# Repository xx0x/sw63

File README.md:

# Space Watch SW63

Sci-fi inspired electronic watch.

*MK4 in the development, out in 2026.*

## How to tell the time?

When the button is briefly pressed, SW63 tells you the time using a sequence of LED blinks. It's not a binary clock, it's inspired by the analog clock hands movement and uses quarters, halves and so on; similar to how people used to tell the time before the digital clock became popular.
  
**16:35**  
*half past - four - hours - and - five - minutes - PM*

**6:57**  
*three - minutes - to - whole - seven - hours*

Language can be changed in the watch menu to reflect the different ways different languages express the time ("half past five" in English is "half of six" in German etc).

See [LANGUAGES.md](./LANGUAGES.md) for the full list and examples.

## Controls

**Short press:** Show the time  
**Long press:** Enter Menu (setting the language and time)  
**Extra long press:** Enter Secret settings  
**Multiple short presses:** Show animation

*In Menu / Secret settings:*  
**Short press:** Change  
**Long press:** Confirm and go to next

## BOM (DIY Kits)

| Name                                | Part Number                                   | Qty |
| ----------------------------------- | --------------------------------------------- | --- |
| PCB with assembled SMD components   | custom part                                   | 1   |
| Red 5 mm LED                        | LL-503VD2E-V1-4D                              | 1   |
| Green 5 mm LED                      | LL-504PGD2E-G5-2B                             | 1   |
| Blue 5 mm LED                       | LL-504BD2E-B4-2B                              | 1   |
| Yellow 5 mm LED                     | N0Y64L35<br> L-53SYD<br> L-53SYDK             | 1   |
| Yellow 3×2 mm LED                   | LL-234YD2Q-1B                                 | 4   |
| Red 3 mm LED                        | FYL-3014LRD1A<br> FYL-3014SRT1A               | 1   |
| Li-Po battery LP301020 or LP301120* | AKY0471<br> SparkFun 13852<br> SparkFun 25270 | 1   |
| CNC aluminium enclosure             | custom part                                   | 1   |
| Screw M1.6 length 4mm (hex socket)  | -                                             | 4   |
| 18 mm watch spring bar              | -                                             | 2   |
| 18 mm watch strap                   | -                                             | 1   |

> [!WARNING]
> \***Note:** Due to the shipping restrictions the Li-Po battery isn't part of the DIY Kit. Please provide your own 40 mAh battery with dimensions 20 mm × 11 mm × 3 mm (or smaller) with the integrated protection circuit.

## License

**Schematics, Hardware Designs**  
CERN-OHL-P-2.0

**Code**  
MIT

**Visual elements, Graphics, Documentation**  
CC BY-SA 4.0

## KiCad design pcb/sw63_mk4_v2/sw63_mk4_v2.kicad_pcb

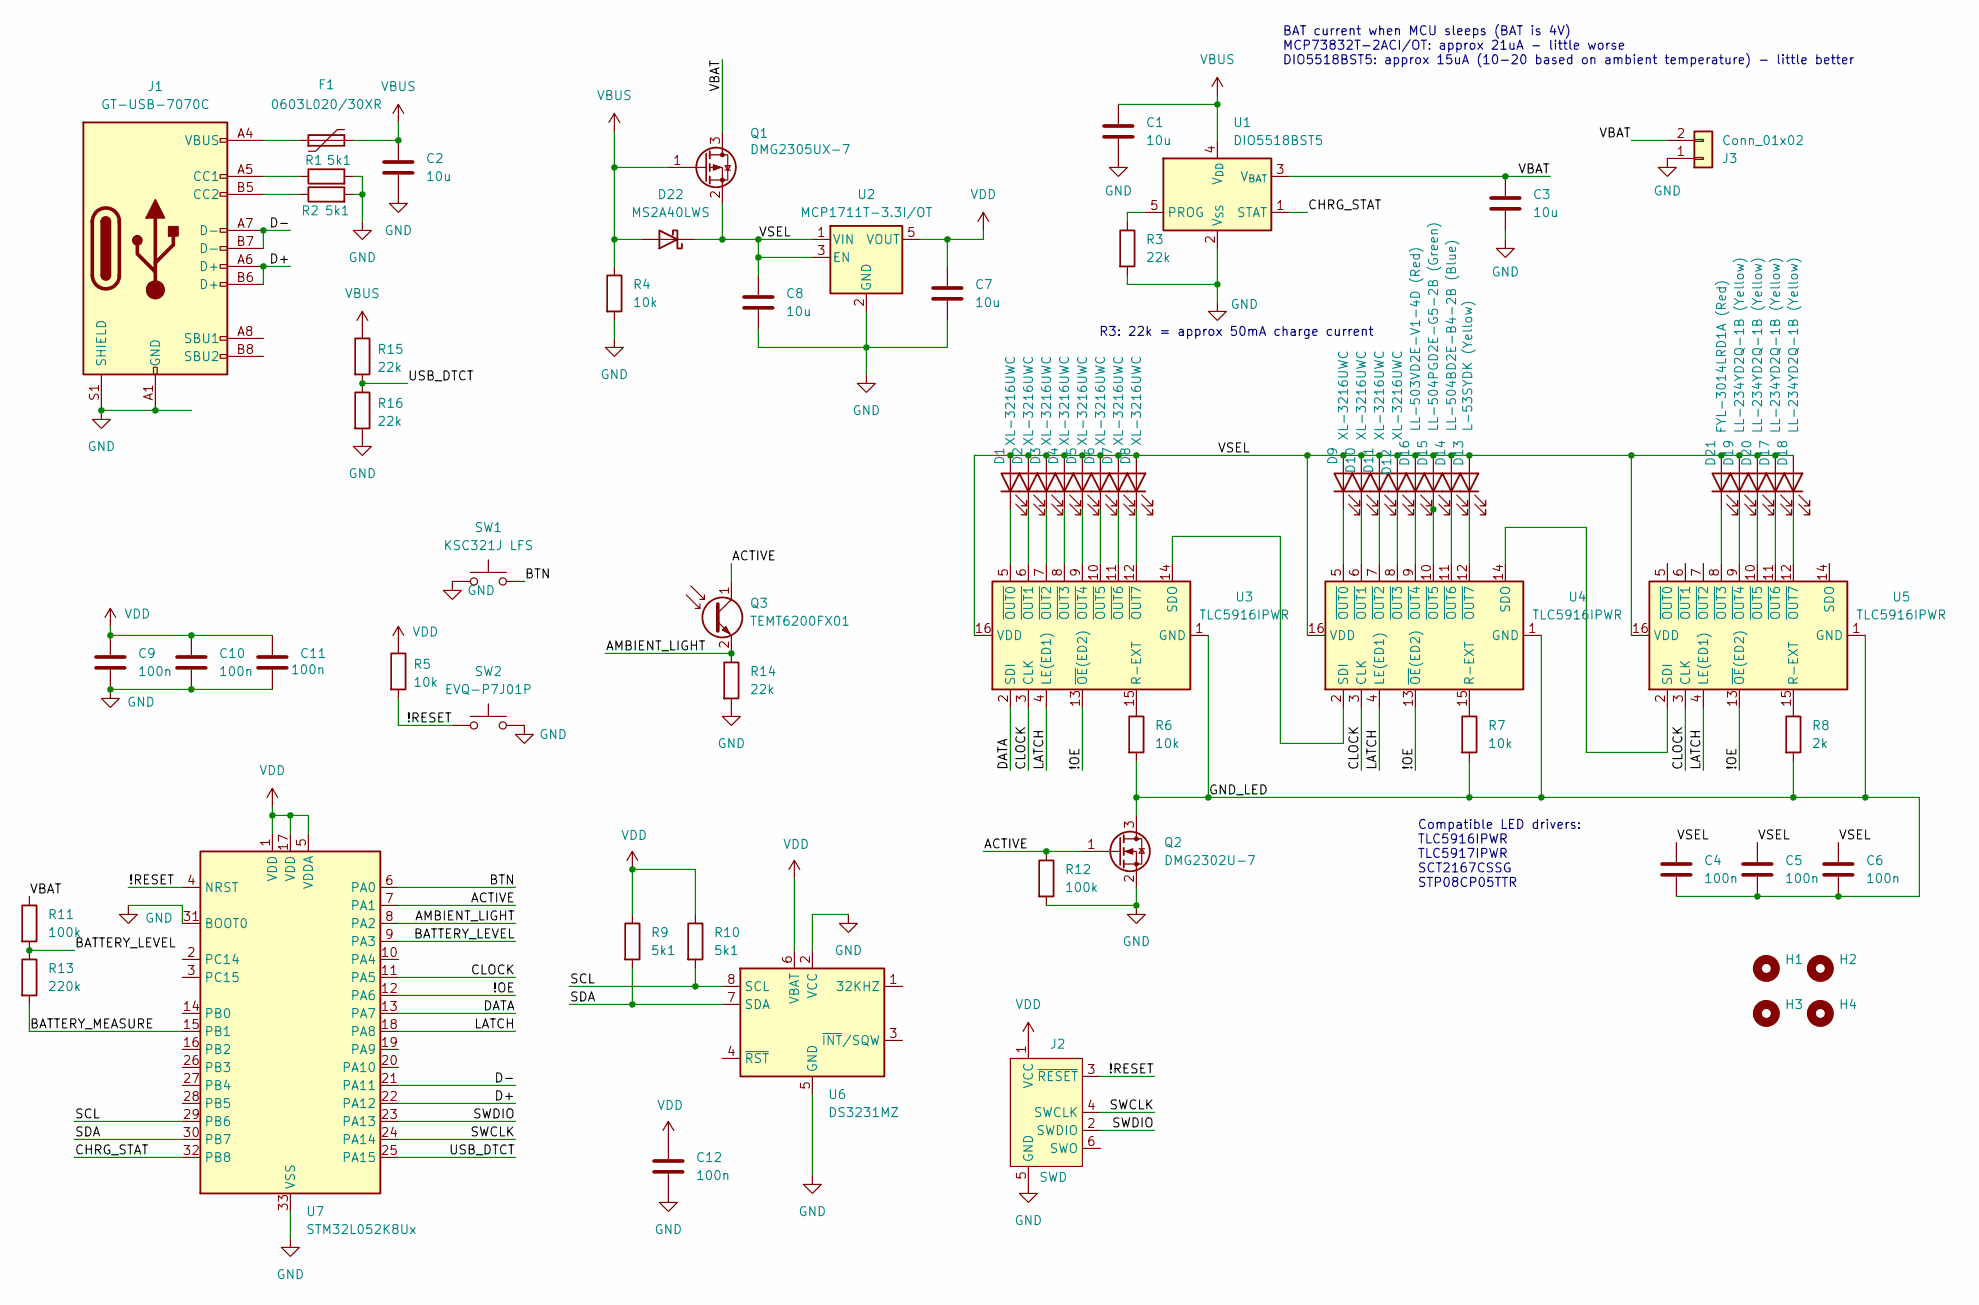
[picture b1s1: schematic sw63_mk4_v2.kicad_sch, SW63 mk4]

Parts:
C1, C2, C3, C7, C8: 10u; C_0402_1005Metric; LCSC C315248
C4, C5, C6, C9, C10, C11, C12: 100n; C_0402_1005Metric; LCSC C1525
D1, D2, D3, D4, D5, D6, D7, D8, D9, D10, D11, D12: XL-3216UWC; LED_1206_W; LCSC C965828
D13: L-53SYDK (Yellow); LED_D5.0mm_Y
D14: LL-504BD2E-B4-2B (Blue); LED_D5.0mm_B
D15: LL-504PGD2E-G5-2B (Green); LED_D5.0mm_G
D16: LL-503VD2E-V1-4D (Red); LED_D5.0mm_R
D17, D18, D19, D20: LL-234YD2Q-1B (Yellow); LED_W3.0mm_H2.0mm_Y
D21: FYL-3014LRD1A (Red); LED_D3.0mm_R
D22: MS2A40LWS; D_SOD-323; LCSC C7380001
F1: 0603L020/30XR; Fuse_0603_1608Metric; LCSC C20608677
H1, H2, H3, H4: MountingHole; MountingHole_1.6mm
J1: GT-USB-7070C; LCSC C5446864
J2: SWD; SWD_2x03_SMD
J3: Conn_01x02; BAT
Q1: DMG2305UX-7; SOT-23; LCSC C150470
Q2: DMG2302U-7; SOT-23
Q3: TEMT6200FX01; LCSC C143695
R1, R2, R9, R10: 5k1; R_0402_1005Metric; LCSC C25905
R3, R14, R15, R16: 22k; R_0402_1005Metric; LCSC C25768
R4, R5, R6, R7: 10k; R_0402_1005Metric; LCSC C25744
R8: 2k; R_0402_1005Metric; LCSC C4109
R11, R12: 100k; R_0402_1005Metric; LCSC C25741
R13: 220k; R_0402_1005Metric; LCSC C25767
SW1: KSC321J LFS; SW_Push_1P1T_NO_CK_KSC3xxJ; LCSC C2798494
SW2: ﻿EVQ-P7J01P; SW_SPST_EVQP7A; LCSC C2828254
U1: DIO5518BST5; SOT-23-5; LCSC C38066
U2: MCP1711T-3.3I/OT; SOT-23-5; LCSC C79527
U3, U4, U5: TLC5916IPWR; TSSOP-16_4.4x5mm_P0.65mm; LCSC C193571
U6: DS3231MZ; SOIC-8_3.9x4.9mm_P1.27mm; LCSC C107410
U7: STM32L052K8Ux; QFN-32-1EP_5x5mm_P0.5mm_EP3.45x3.45mm; LCSC C1342049

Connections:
/!OE: U3.13 (~OE(ED2)), U4.13 (~OE(ED2)), U5.13 (~OE(ED2)), U7.12 (PA6)
/!RESET: J2.3 (~RESET), R5.2, SW2.1, U7.4 (NRST)
/ACTIVE: Q2.1 (G), Q3.1 (C), R12.1, U7.7 (PA1)
/AMBIENT_LIGHT: Q3.2 (E), R14.1, U7.8 (PA2)
/BATTERY_LEVEL: R11.2, R13.1, U7.9 (PA3)
/BATTERY_MEASURE: R13.2, U7.15 (PB1)
/BTN: SW1.2, U7.6 (PA0)
/CHRG_STAT: U1.1 (STAT), U7.32 (PB8)
/CLOCK: U3.3 (CLK), U4.3 (CLK), U5.3 (CLK), U7.11 (PA5)
/D+: J1.A6 (D+), J1.B6 (D+), U7.22 (PA12)
/D-: J1.A7 (D-), J1.B7 (D-), U7.21 (PA11)
/DATA: U3.2 (SDI), U7.13 (PA7)
/GND_LED: C4.2, C5.2, C6.2, Q2.3 (D), R6.2, R7.2, R8.2, U3.1 (GND), U4.1 (GND), U5.1 (GND)
/LATCH: U3.4 (LE(ED1)), U4.4 (LE(ED1)), U5.4 (LE(ED1)), U7.18 (PA8)
/SCL: R10.2, U6.8 (SCL), U7.29 (PB6)
/SDA: R9.2, U6.7 (SDA), U7.30 (PB7)
/SWCLK: J2.4 (SWCLK), U7.24 (PA14)
/SWDIO: J2.2 (SWDIO), U7.23 (PA13)
/USB_DTCT: R15.2, R16.1, U7.25 (PA15)
/VBAT: C3.1, J3.2, Q1.3 (D), R11.1, U1.3 (V_{BAT})
/VSEL: C4.1, C5.1, C6.1, C8.1, D1.2 (A), D2.2 (A), D3.2 (A), D4.2 (A), D5.2 (A), D6.2 (A), D7.2 (A), D8.2 (A), D9.2 (A), D10.2 (A), D11.2 (A), D12.2 (A), D13.2 (A), D14.2 (A), D15.2 (A), D16.2 (A), D17.2 (A), D18.2 (A), D19.2 (A), D20.2 (A), D21.2 (A), D22.1 (K), Q1.2 (S), U2.1 (VIN), U2.3 (EN), U3.16 (VDD), U4.16 (VDD), U5.16 (VDD)
GND: C1.2, C2.2, C3.2, C7.2, C8.2, C9.2, C10.2, C11.2, C12.2, J1.A1 (GND), J1.A12 (GND), J1.B1 (GND), J1.B12 (GND), J1.S1 (SHIELD), J2.5 (GND), J3.1, Q2.2 (S), R1.2, R2.2, R3.2, R4.2, R12.2, R14.2, R16.2, SW1.1, SW2.2, U1.2 (V_{SS}), U2.2 (GND), U6.2 (VCC), U6.5 (GND), U7.31 (BOOT0), U7.33 (VSS)
unnamed: D1.1 (K), U3.5 (~OUT0)
unnamed: D2.1 (K), U3.6 (~OUT1)
unnamed: D3.1 (K), U3.7 (~OUT2)
unnamed: D4.1 (K), U3.8 (~OUT3)
unnamed: D5.1 (K), U3.9 (~OUT4)
unnamed: D6.1 (K), U3.10 (~OUT5)
unnamed: D7.1 (K), U3.11 (~OUT6)
unnamed: D8.1 (K), U3.12 (~OUT7)
unnamed: D9.1 (K), U4.5 (~OUT0)
unnamed: D10.1 (K), U4.6 (~OUT1)
unnamed: D11.1 (K), U4.7 (~OUT2)
unnamed: D12.1 (K), U4.8 (~OUT3)
unnamed: D13.1 (K), U4.12 (~OUT7)
unnamed: D14.1 (K), U4.11 (~OUT6)
unnamed: D15.1 (K), U4.10 (~OUT5)
unnamed: D16.1 (K), U4.9 (~OUT4)
unnamed: D17.1 (K), U5.11 (~OUT6)
unnamed: D18.1 (K), U5.12 (~OUT7)
unnamed: D19.1 (K), U5.9 (~OUT4)
unnamed: D20.1 (K), U5.10 (~OUT5)
unnamed: D21.1 (K), U5.8 (~OUT3)
unnamed: F1.1, J1.A4 (VBUS), J1.A9 (VBUS), J1.B4 (VBUS), J1.B9 (VBUS)
unnamed: J1.A5 (CC1), R1.1
unnamed: J1.B5 (CC2), R2.1
unnamed: R3.1, U1.5 (PROG)
unnamed: R6.1, U3.15 (R-EXT)
unnamed: U3.14 (SDO), U4.2 (SDI)
unnamed: R7.1, U4.15 (R-EXT)
unnamed: U4.14 (SDO), U5.2 (SDI)
unnamed: R8.1, U5.15 (R-EXT)
VBUS: C1.1, C2.1, D22.2 (A), F1.2, Q1.1 (G), R4.1, R15.1, U1.4 (V_{DD})
VDD: C7.1, C9.1, C10.1, C11.1, C12.1, J2.1 (VCC), R5.1, R9.1, R10.1, U2.5 (VOUT), U6.6 (VBAT), U7.1 (VDD), U7.5 (VDDA), U7.17 (VDD)

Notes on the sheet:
BAT current when MCU sleeps (BAT is 4V) MCP73832T-2ACI/OT: approx 21uA - little worse DIO5518BST5: approx 15uA (10-20 based on ambient temperature) - little better
R3: 22k = approx 50mA charge current
Compatible LED drivers: TLC5916IPWR TLC5917IPWR SCT2167CSSG STP08CP05TTR

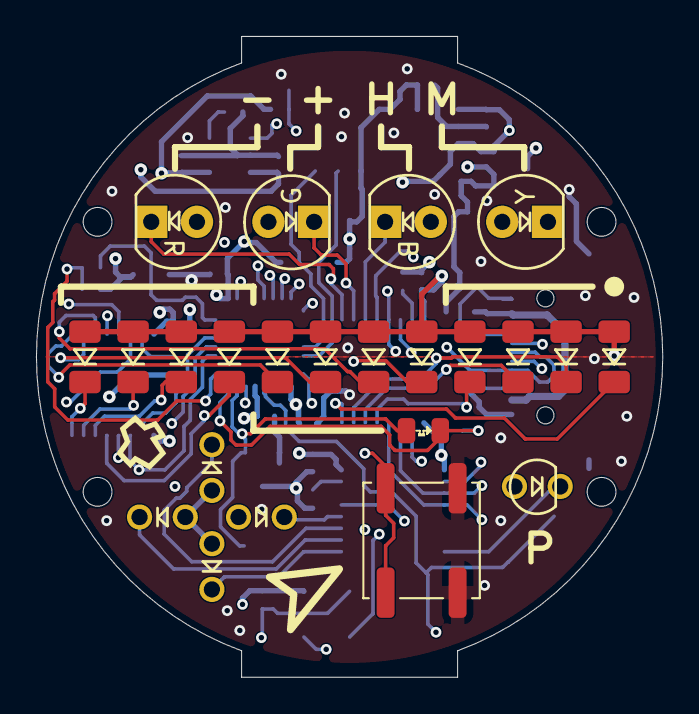
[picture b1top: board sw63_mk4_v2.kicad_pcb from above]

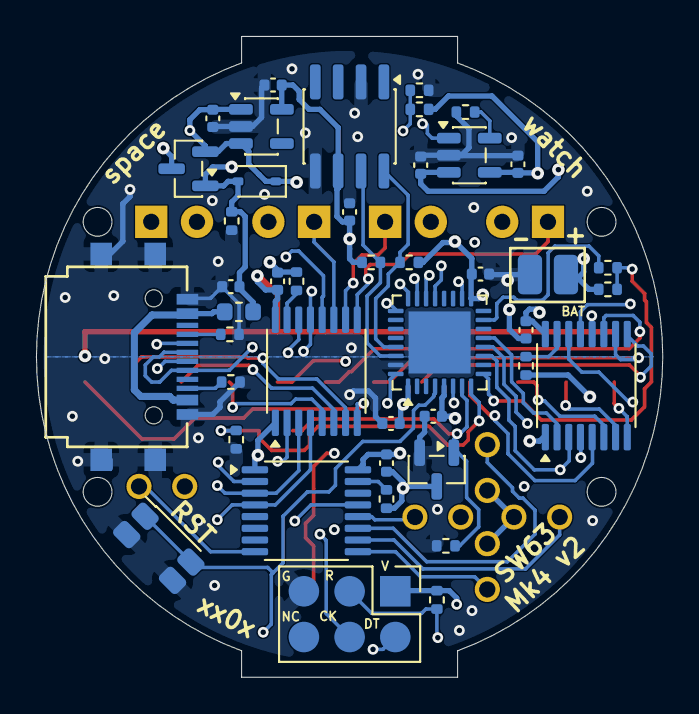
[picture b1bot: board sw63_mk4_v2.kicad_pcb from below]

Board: 4 copper layers, 34.8 x 35.6 mm, 70 parts (43 on the bottom side), 54 nets.

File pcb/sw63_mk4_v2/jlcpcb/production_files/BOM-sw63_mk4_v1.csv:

Comment,Designator,Footprint,LCSC,Quantity
0603L020/30XR,F1,Fuse_0603_1608Metric,C20608677,1
100k,"R11,R12",R_0402_1005Metric,C25741,2
100n,"C10,C11,C12,C4,C5,C6,C9",C_0402_1005Metric,C1525,7
10k,"R4,R5,R6,R7",R_0402_1005Metric,C25744,4
10u,"C1,C2,C3,C7,C8",C_0402_1005Metric,C315248,5
220k,R13,R_0402_1005Metric,C25767,1
22k,"R14,R15,R16,R3",R_0402_1005Metric,C25768,4
2k,R8,R_0402_1005Metric,C4109,1
5k1,"R1,R10,R2,R9",R_0402_1005Metric,C25905,4
DIO5518BST5,U1,SOT-23-5,C38066,1
DMG2302U-7,Q2,SOT-23,C96613,1
DMG2305UX-7,Q1,SOT-23,C150470,1
DS3231MZ,U6,SOIC-8_3.9x4.9mm_P1.27mm,C107410,1
GT-USB-7070C,J1,GT-USB-7070C,C5446864,1
KSC321J LFS,SW1,SW_Push_1P1T_NO_CK_KSC3xxJ,C2798494,1
LED,"D1,D10,D11,D12,D2,D3,D4,D5,D6,D7,D8,D9",LED_1206_W,C965828,12
MCP1711T-3.3I/OT,U2,SOT-23-5,C79527,1
MS2A40LWS,D22,D_SOD-323,C7380001,1
STM32L052K8Ux,U7,QFN-32-1EP_5x5mm_P0.5mm_EP3.45x3.45mm,C1342049,1
TEMT6200FX01,Q3,TEMT6200FX01,C143695,1
TLC5916IPWR,"U3,U4,U5",TSSOP-16_4.4x5mm_P0.65mm,C193571,3
﻿EVQ-P7J01P,SW2,SW_SPST_EVQP7A,C2828254,1
LED,D14,LED_D5.0mm_B,,1
LED,D16,LED_D5.0mm_R,,1
LED,D21,LED_D3.0mm_R,,1
LED,D20,LED_W3.0mm_H2.0mm_Y,,1
LED,D18,LED_W3.0mm_H2.0mm_Y,,1
LED,D13,LED_D5.0mm_Y,,1
LED,D15,LED_D5.0mm_G,,1
LED,D19,LED_W3.0mm_H2.0mm_Y,,1
LED,D17,LED_W3.0mm_H2.0mm_Y,,1

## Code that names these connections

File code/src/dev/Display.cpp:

#include "Display.hpp"
#include "app/App.hpp"
#include "utils/math_utils.hpp"
#include <algorithm>

void Display::Init()
{
    // Prevent startup LED driver glitches
    brightness_.PreInit();

    // Enable display power
    SetPower(true);

    // Initialize ambient light sensor (PA2)
    ambient_light_.Init({.port = GPIOA,
                         .pin = GPIO_PIN_2,
                         .channel = ADC_CHANNEL_2});

    // Shift register for LEDs
    display_register_.Init({
        .data = {GPIOA, GPIO_PIN_7},  // MOSI - PA7
        .clock = {GPIOA, GPIO_PIN_5}, // SCK - PA5
        .latch = {GPIOA, GPIO_PIN_8}  // LATCH - PA8
    });

    // Clear display state
    Clear();

    // Update display
    Update();

    // Initialize PWM brightness control
    brightness_.Init();

    // Set brightness based on ambient light
    TriggerAutoBrightness();
}

void Display::SetPower(bool on)
{
    if (on)
    {
        GPIO_InitTypeDef GPIO_InitStruct = {
            .Pin = kDisplayEnablePin.pin,
            .Mode = GPIO_MODE_OUTPUT_PP,
            .Pull = GPIO_NOPULL,
            .Speed = GPIO_SPEED_FREQ_VERY_HIGH,
            .Alternate = 0,
        };
        HAL_GPIO_Init(kDisplayEnablePin.port, &GPIO_InitStruct);
        HAL_GPIO_WritePin(kDisplayEnablePin.port, kDisplayEnablePin.pin, GPIO_PIN_SET);
    }
    else
    {
        HAL_GPIO_DeInit(kDisplayEnablePin.port, kDisplayEnablePin.pin);
    }
}

void Display::DeInit()
{
    Clear();
    Update();
    brightness_.DeInit();
    ambient_light_.DeInit();
    display_register_.DeInit();
    SetPower(false);
}

void Display::TriggerAutoBrightness()
{
    // Read ambient light from PA02 (ADC channel 2)
    auto ambient_result = ambient_light_.ReadSingleShot();
    if (!ambient_result.has_value())
    {
        // ADC read failed, use default brightness
        brightness_.Set(kMaxBrightness / 2);
        return;
    }
    uint16_t ambient_reading = ambient_result.value();

    // Map the ADC reading using a linear mapping table
    // Makes it lighter in dark light compared to a direct mapping (also prevents 0 brightness)
    static constexpr MapDef<int, 5> kBrightnessMap = {
        {0, 512, 2048, 3072, 4095}, // in
        {16, 1024, 2048, 3072, 4095}}; // out
    uint16_t mapped_brightness = curve_map(ambient_reading, kBrightnessMap, MapClamp::TRUE);

    // Set the brightness
    brightness_.Set(mapped_brightness);
}

void Display::Clear()
{
    data_.reset();
}

void Display::Update()
{
    display_register_.Write(data_);
}

void Display::SetClockFace(ClockFace face)
{
    data_.set(static_cast<size_t>(Led::UP), ClockFace::UP == face);
    data_.set(static_cast<size_t>(Led::RIGHT), ClockFace::RIGHT == face);
    data_.set(static_cast<size_t>(Led::DOWN), ClockFace::DOWN == face);
    data_.set(static_cast<size_t>(Led::LEFT), ClockFace::LEFT == face);
}

void Display::SetPm(bool on)
{
    data_.set(static_cast<size_t>(Led::PM), on);
}

void Display::SetTopLed(TopLed led)
{
    data_.set(static_cast<size_t>(Led::HOURS), TopLed::HOURS == led);
    data_.set(static_cast<size_t>(Led::MINUTES), TopLed::MINUTES == led);
    data_.set(static_cast<size_t>(Led::AFTER), TopLed::AFTER == led);
    data_.set(static_cast<size_t>(Led::BEFORE), TopLed::BEFORE == led);
}

void Display::SetNumber(size_t number, NumStyle style)
{
    if (style == NumStyle::COUNT)
    {
        style = App::settings.GetConfig().num_style;
    }

    for (auto led : kNumLeds)
    {
        data_.set(static_cast<size_t>(led), false);
    }
    if (number == 0 || number > kNumLedCount)
    {
        return;
    }

    switch (style)
    {
    case NumStyle::SINGLE:
        data_.set(static_cast<size_t>(kNumLeds[number - 1]), true);
        break;

    case NumStyle::SINGLE_REVERSED:
        data_.set(static_cast<size_t>(kRevNumLeds[number - 1]), true);
        break;

    case NumStyle::BAR:
        for (size_t i = 0; i < number; ++i)
        {
            data_.set(static_cast<size_t>(kNumLeds[i]), true);
        }
        break;
    case NumStyle::BAR_REVERSED:
        for (size_t i = 0; i < number; ++i)
        {
            data_.set(static_cast<size_t>(kRevNumLeds[i]), true);
        }
        break;
    case NumStyle::SNAKE:
        data_.set(static_cast<size_t>(kNumLeds[number - 1]), true);
        data_.set(static_cast<size_t>(kNumLeds[number % Display::kNumLedCount]), true);
        data_.set(static_cast<size_t>(kNumLeds[(number + 1) % Display::kNumLedCount]), true);
        break;
    case NumStyle::SNAKE_REVERSED:
        data_.set(static_cast<size_t>(kRevNumLeds[number - 1]), true);
        data_.set(static_cast<size_t>(kRevNumLeds[number % Display::kNumLedCount]), true);
        data_.set(static_cast<size_t>(kRevNumLeds[(number + 1) % Display::kNumLedCount]), true);
        break;
    case NumStyle::COUNT:
    default:
        break;
    }
}

void Display::SetLed(Led led, bool on)
{
    data_.set(static_cast<size_t>(led), on);
}

void Display::TestProcedure()
{
    // Just for the development!!!
    // The intro animation is something different
    for (int i = 0; i <= 12; i++)
    {
        Clear();
        SetNumber(i);
        Update();
        HAL_Delay(200);
    }

    for (auto top_led : EnumRange<Display::TopLed>())
    {
        Clear();
        SetTopLed(top_led);
        Update();
        HAL_Delay(200);
    }

    for (auto clockface : EnumRange<Display::ClockFace>())
    {
        Clear();
        SetClockFace(clockface);
        Update();
        HAL_Delay(200);
    }

    for (int i = 0; i < 3; i++)
    {
        Clear();
        SetPm(true);
        Update();
        HAL_Delay(200);
        SetPm(false);
        Update();
        HAL_Delay(200);
    }
}

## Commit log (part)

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2019-12-08 initial sw63 commit
2019-12-08 add schematic
2019-12-08 add charger schematic
2019-12-30 add compiled firmware in HEX format
2019-12-30 add build instructions link
2019-12-30 add video presentation link to readme
2020-05-29 add pcb sources and 3d files
2020-05-29 add Czech manual
2020-07-21 brightness update for v2
2020-08-06 add speed, saver, compressed variant, remove French
2020-08-06 speed updates
2020-08-06 timestart at 00:00
2020-08-12 button handling update
2021-06-11 update readme and schematics
2021-06-11 cleanup, remove old files
2024-08-12 add sw63 mk3 initial schematic + layout
2024-08-13 finishing schematics
2024-08-13 routing done
2024-08-13 layout tweaks
2024-08-13 add graphics
2024-08-14 layout changes for better case compatibility
2024-08-14 update led colors to match reality
2024-08-14 final board touches
2024-08-25 board update
2024-09-01 add bottom graphics
2024-09-01 mk3 coding begin
2024-09-01 add sleep
2024-09-01 implementing animations
2024-09-01 time displaying
2024-09-01 schematic notes
2024-09-01 animations update, add charging animation etc.
2024-11-29 3_2 in progress
2024-11-29 3_2 update
2025-01-15 add 3_2 board files
2025-05-04 basic rust code example
2025-05-04 cleanup, button reading
2025-05-04 working ds3231 example
2025-05-04 implement adc reading
2025-05-04 faking deep sleep for now
2025-05-04 button reading using interrupt
2025-05-04 deep sleep (ugly but kinda works)
2025-05-04 cleanup
2026-01-26 archive old stuff
2026-01-26 begin mk4 schematic
2026-01-26 layout in progress
2026-01-26 update gitignore
2026-01-26 update board
2026-01-28 update models and footprints
2026-01-28 routing in progress
2026-01-28 routing
2026-01-28 routing, graphics
2026-01-28 updated models
2026-01-29 add usb dtct
2026-01-29 panelization prepare
2026-01-29 mfg data
2026-01-30 add case graphics
2026-02-02 update case & graphics
2026-02-02 add submodules for code
2026-02-02 add actual submodules
2026-02-02 add .clang-format
2026-02-02 initial MK4 code commit
2026-02-02 end charge animation when charging done
2026-02-02 AnimationRunner handles timings
2026-02-02 add layer and event support
2026-02-02 update layer support
2026-02-02 add Button class
2026-02-02 update button behavior
2026-02-02 update layer stuff
2026-02-02 double tap to run speed 0
2026-02-02 params tweaking
2026-02-06 bug note
2026-02-06 update for new wiring
2026-02-06 working charge animation
2026-02-06 slower brightness pwm to prevent glitches
2026-02-06 do auto brightness always between frames
2026-02-06 remove double press (was too complicated)
2026-02-06 add power detection
2026-02-06 retry rtc init on startup few times
2026-02-06 simplify date/time
2026-02-07 charge animation cleanup
2026-02-07 rename SHORT_PRESS to JUST_PRESSED
2026-02-07 implement JUST_RELEASED
2026-02-07 working time setting
2026-02-07 cleaner time setting
2026-02-07 cleaner time setting 2
2026-02-07 cleaner time setting 3
2026-02-07 added secret menu
2026-02-07 timing tweaks
2026-02-07 fix warnings
2026-02-07 add custom System::Millis() function
2026-02-07 cleanup button
2026-02-07 add timeout for other than LayerNormal
2026-02-07 move animation type into runner
2026-02-07 move AnimationRunner into LayerNormal
2026-02-07 reorganize LayerNormal events
2026-02-07 AnimationIntro followed by DisplayTime
2026-02-07 low battery indication before sleep
2026-02-07 add battery level display to the secret menu
2026-02-07 add uf2 submodule
2026-02-07 add uf2 output to build process
2026-02-07 default time as 00:00:00
2026-02-07 add bootloader and tasks
2026-02-08 move all settings into the Settings class
2026-02-08 visual style settings
2026-02-08 higher overall brightness
2026-02-08 add tinyusb submodule
2026-02-08 vibe coded serial communication
2026-02-08 add DISPLAY_TIME command, add commands to tasks
2026-02-08 invert charge complete blink cycle
2026-02-08 updated bootloader
2026-02-08 rename bootloader readme
2026-02-08 update bootloader readme
2026-02-08 simplify communication and docs
2026-02-17 remove the 2* brightness (was too bright)
2026-02-17 fix LED driver startup glitch (hopefully)
2026-02-17 add linux vscode config
2026-03-07 add v2 pcb with fixed mosfet
2026-03-07 remove v1 pcb
2026-03-07 slightly smaller pcb, better fit in the enclosure
2026-03-12 updated pcb info
2026-03-12 updated production files
2026-03-12 move the python communication into its' own folder
2026-03-12 remove automatic pcb backups from git
2026-03-12 add backups to gitignore
2026-03-12 basic vite + react project
2026-03-12 quick communication app, ugly but works somehow
2026-03-12 separate SW63Client class
2026-03-12 add config options, dynamically loaded
2026-03-12 implement GET_VERSION
2026-03-12 renumber commands
2026-03-12 set the time +15s (same as in python)
2026-03-12 actual ticking time
2026-03-12 app tweaks
2026-03-13 more speed settings
2026-03-13 update usb stuff
2026-03-13 react app description
2026-03-13 add DISPLAY_INTRO message
2026-03-13 cleanup copy paste code
2026-03-13 rename GET_CONFIG_OPTIONS to GET_CONFIG_OPTION_VALUES
2026-03-13 add single option get/set support
2026-03-13 disconnect when not available
2026-03-24 basic com styling
2026-03-24 style updates
2026-03-26 add logo
2026-03-26 style tweaks
2026-03-26 add log
2026-03-26 log autoscroll
2026-03-26 favicon
2026-03-26 Log is a separate component now
2026-03-26 scrollbar styling
2026-03-26 add app language dropdown (doesn't do anything now)
2026-03-26 add cs, en translations
2026-03-26 translating options
2026-03-26 more translations
2026-03-26 translation update
2026-03-26 log tweaks
2026-03-27 change settings order and naming
2026-03-27 add slowest/fastest speed label
2026-03-27 change version to 0.9
2026-03-27 doxygen comments
2026-03-27 main lincense and cleanup
2026-03-27 fix base url
2026-03-27 update sw63 image, add to readme
2026-03-27 rename archive_junk to .archive
2026-03-28 npm audit fix
2026-03-29 ukraninan translation updates
2026-03-29 languages update
2026-03-29 info button next to languages doesn't do anything now
2026-03-29 fix up language sequences for Polish
2026-04-16 update part names and docs
2026-04-16 add bom
2026-04-16 update to Kicad 10
2026-04-16 readme tweaks
2026-04-16 readme tweaks, add languages doc
2026-04-18 add flashing script
2026-04-25 update vscode configs
2026-04-25 update license year and name
2026-04-25 bump version to 0.9.1
2026-04-26 npm audit
2026-04-27 schematic notes and pdf
2026-05-14 add "-NoGui 1" for faster J-Link upload

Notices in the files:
pcb/sw63_mk4_v2/sw63_mk4_v2.kicad_pcb:
License: CERN-OHL-P-2.0
